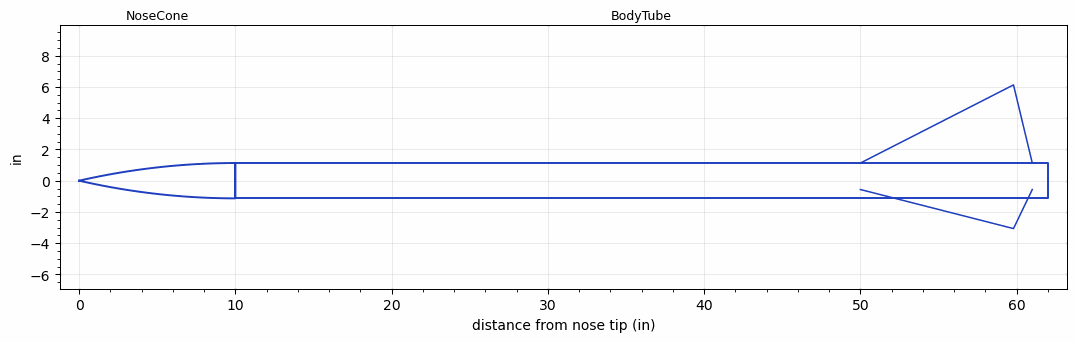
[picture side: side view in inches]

<RASAeroDocument>
 <FileVersion>2</FileVersion>
 <RocketDesign>
  <NoseCone>
   <Length>10</Length>
   <Diameter>2.26</Diameter>
   <Shape>Tangent Ogive</Shape>
   <Location>0</Location>
  </NoseCone>
  <BodyTube>
   <Length>52</Length>
   <Diameter>2.26</Diameter>
   <Location>10</Location>
   <Fin>
    <Count>3</Count>
    <Chord>11</Chord>
    <Span>5</Span>
    <SweepDistance>9.798</SweepDistance>
    <TipChord>0</TipChord>
    <Thickness>0.125</Thickness>
    <Location>12</Location>
    <AirfoilSection>Hexagonal</AirfoilSection>
    <FX1>0.66</FX1>
    <FX3>0.3</FX3>
   </Fin>
  </BodyTube>
  <Surface>Smooth (Zero Roughness)</Surface>
  <ModifiedBarrowman>False</ModifiedBarrowman>
  <Turbulence>False</Turbulence>
  <SustainerNozzle>1</SustainerNozzle>
  <UseBooster1>False</UseBooster1>
  <UseBooster2>False</UseBooster2>
  <Comments>Kline-Rogers L500 Rocket
Ace Aeronautics SIngle-Use "D" Grain L500 Motor
USXRL-89

Optical Track
Altitude = 24771 ft

RASAero II Prediction = 26509 ft
Error = 7.02%
</Comments>
 </RocketDesign>
 <LaunchSite>
  <Altitude>2848</Altitude>
  <Pressure>0</Pressure>
  <RodAngle>0</RodAngle>
  <RodLength>8</RodLength>
  <Temperature>80</Temperature>
  <WindSpeed>0</WindSpeed>
 </LaunchSite>
 <Recovery>
  <Altitude1>1000</Altitude1>
  <Altitude2>1000</Altitude2>
  <DeviceType1>Parachute</DeviceType1>
  <DeviceType2>Chute</DeviceType2>
  <Event1>False</Event1>
  <Event2>False</Event2>
  <Size1>36</Size1>
  <Size2>100</Size2>
  <EventType1>Apogee</EventType1>
  <EventType2>None</EventType2>
  <CD1>1.33</CD1>
  <CD2>1.33</CD2>
 </Recovery>
 <SimulationList>
  <Simulation>
   <SustainerEngine>L500  (Hist)</SustainerEngine>
   <SustainerLaunchWt>8.5</SustainerLaunchWt>
   <SustainerNozzleDiameter>1</SustainerNozzleDiameter>
   <SustainerCG>42.6</SustainerCG>
   <SustainerIgnitionDelay>0</SustainerIgnitionDelay>
   <Booster1SeparationDelay>0</Booster1SeparationDelay>
   <Booster1IgnitionDelay>0</Booster1IgnitionDelay>
   <IncludeBooster1>False</IncludeBooster1>
   <Booster2Delay>0</Booster2Delay>
   <IncludeBooster2>False</IncludeBooster2>
   <TimetoApogee>34.12028</TimetoApogee>
   <MaxAltitude>26509</MaxAltitude>
   <MaxVelocity>2229.373</MaxVelocity>
  </Simulation>
 </SimulationList>
</RASAeroDocument>
